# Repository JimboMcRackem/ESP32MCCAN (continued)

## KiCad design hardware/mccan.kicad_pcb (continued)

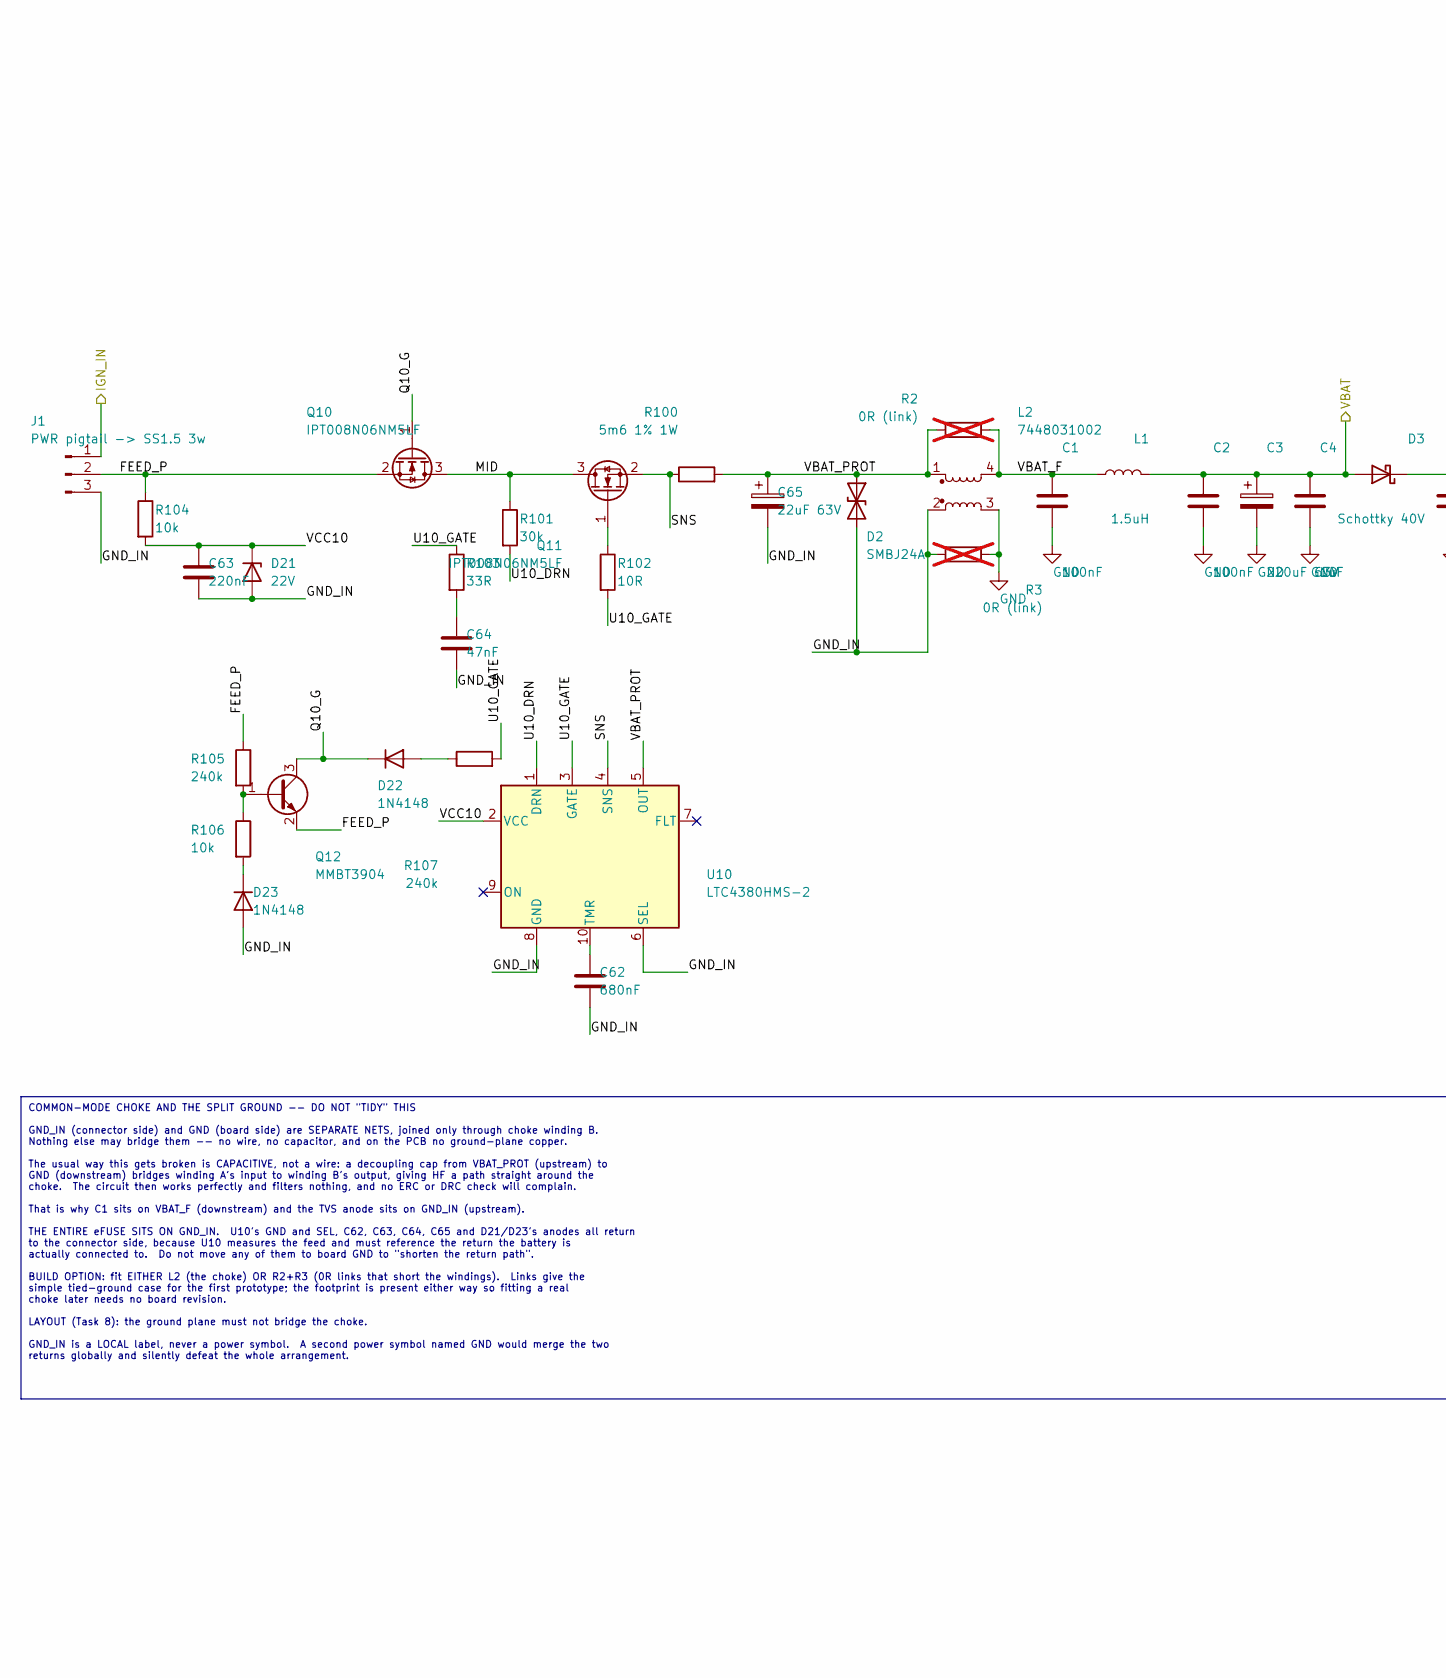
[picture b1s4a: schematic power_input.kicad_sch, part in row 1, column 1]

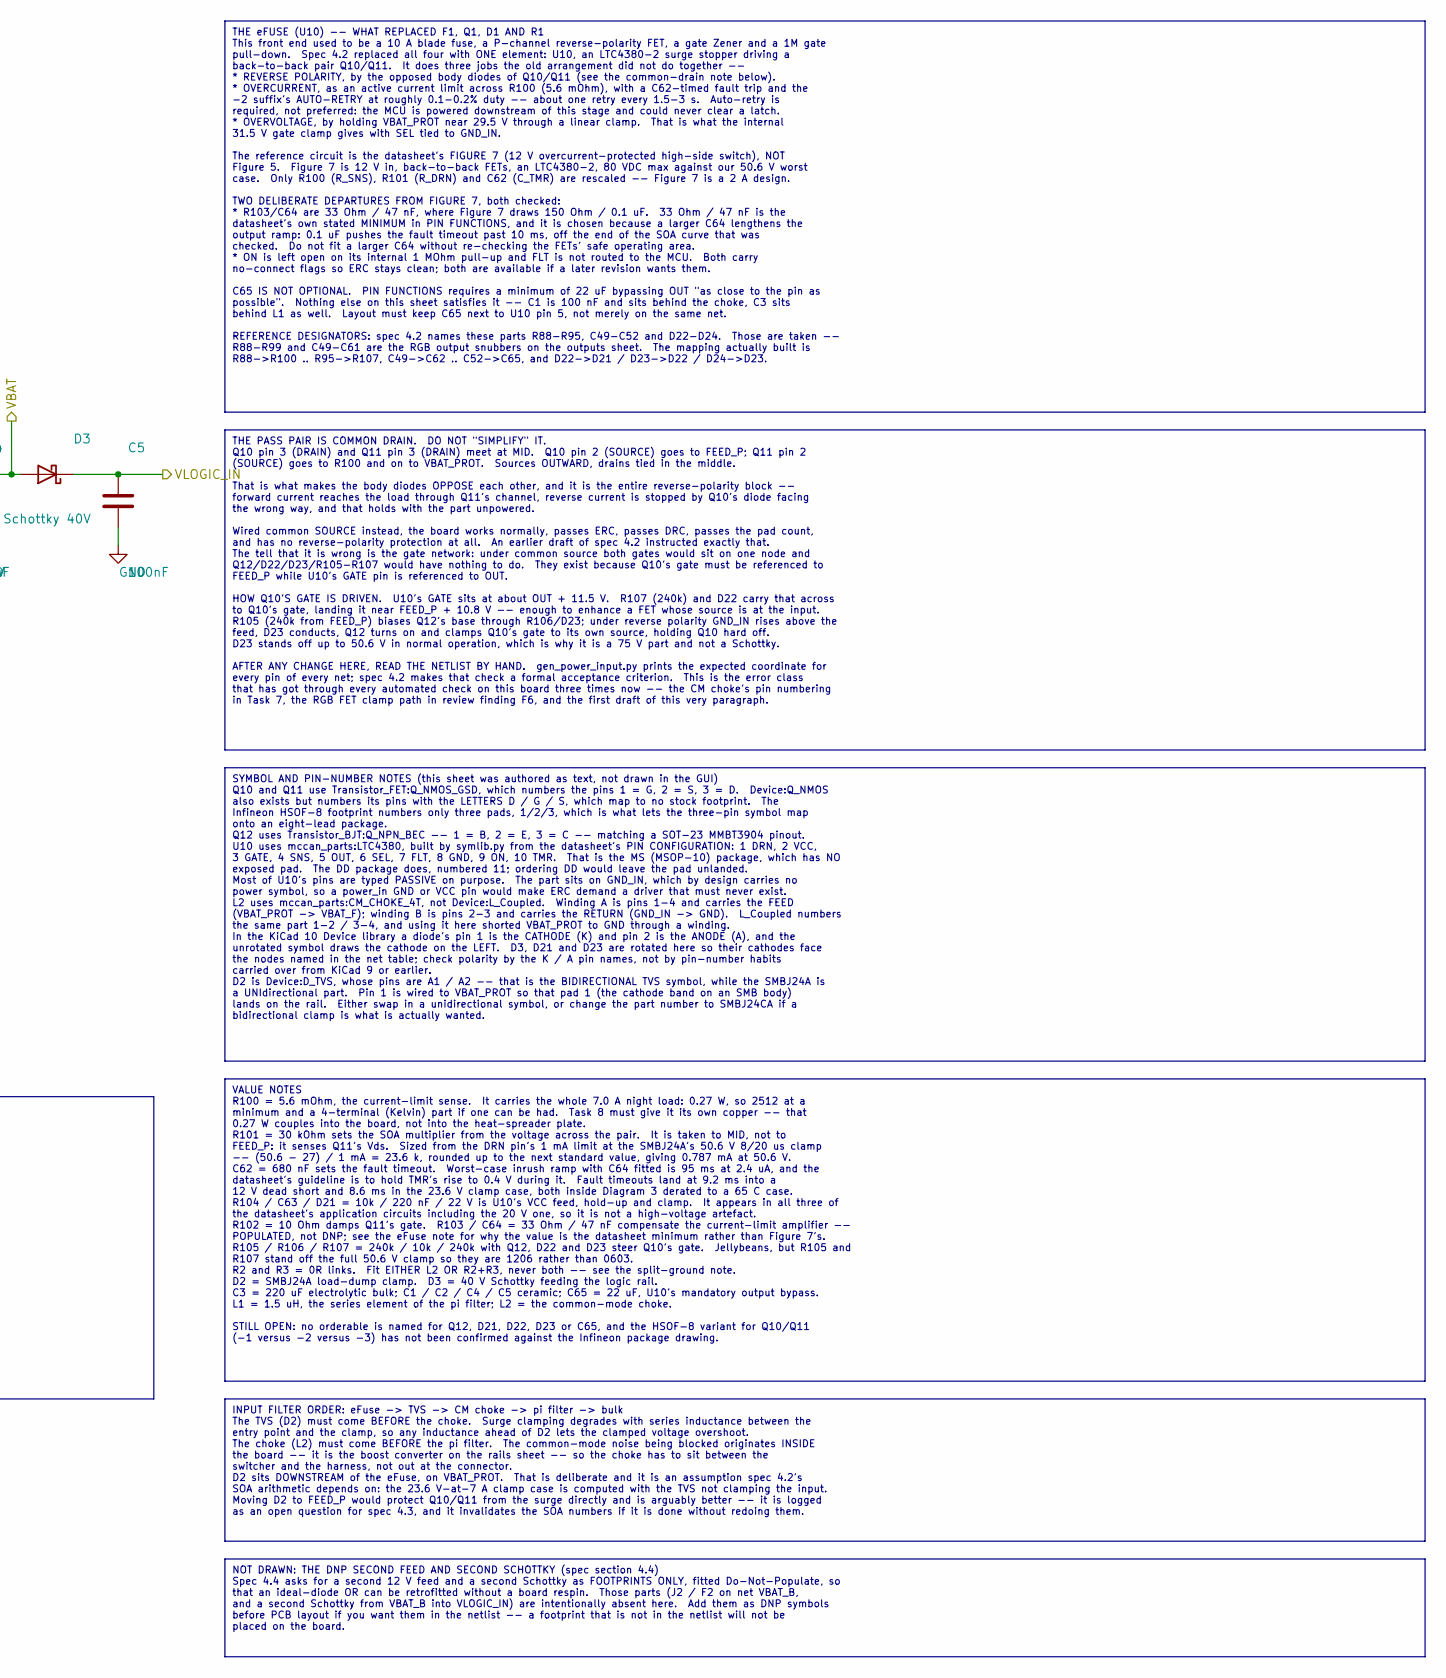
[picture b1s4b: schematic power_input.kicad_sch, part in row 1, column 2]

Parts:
C1: 100nF; C_0603_1608Metric
C2, C5: 100nF; C_0805_2012Metric
C3: 220uF 63V; CP_Elec_10x10.5
C4: 1uF; C_1206_3216Metric
C62: 680nF; C_0603_1608Metric
C63: 220nF; C_0603_1608Metric
C64: 47nF; C_0805_2012Metric
C65: 22uF 63V; CP_Elec_6.3x7.7
D2: SMBJ24A; D_SMB
D3: Schottky 40V; D_SMA
D21: 22V; D_SOD-123
D22, D23: 1N4148; D_SOD-323
J1: PWR pigtail -> SS1.5 3w; SolderWire-1.5sqmm_1x03_P6mm_D1.7mm_OD3mm_Relief
L1: 1.5uH; L_Vishay_IHLP-4040
L2: 7448031002; Wurth_WE-CMBNC_7448031002
Q10, Q11: IPT008N06NM5LF; Infineon_PG-HSOF-8-1
Q12: MMBT3904; SOT-23
R2, R3: 0R (link); R_2512_6332Metric; not fitted
R100: 5m6 1% 1W; R_2512_6332Metric
R101: 30k; R_1206_3216Metric
R102: 10R; R_0603_1608Metric
R103: 33R; R_0603_1608Metric
R104, R106: 10k; R_0603_1608Metric
R105, R107: 240k; R_1206_3216Metric
U10: LTC4380HMS-2; MSOP-10_3x3mm_P0.5mm

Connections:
/IGN_IN: J1.1; also elsewhere on the board
/VBAT: C2.1, C3.1, C4.1, D3.2 (A), L1.2; also elsewhere on the board
/VLOGIC_IN: C5.1, D3.1 (K); also elsewhere on the board
/power_input/FEED_P: J1.2, Q10.2 (S), Q12.2 (E), R104.1, R105.1
/power_input/GND_IN: C62.2, C63.2, C64.2, C65.2, D2.2 (A2), D21.2 (A), D23.2 (A), J1.3, L2.2, R3.1, U10.6 (SEL), U10.8 (GND)
/power_input/MID: Q10.3 (D), Q11.3 (D), R101.1
/power_input/Q10_G: D22.1 (K), Q10.1 (G), Q12.3 (C)
/power_input/SNS: Q11.2 (S), R100.1, U10.4 (SNS)
/power_input/U10_DRN: R101.2, U10.1 (DRN)
/power_input/U10_GATE: R102.2, R103.1, R107.2, U10.3 (GATE)
/power_input/VBAT_F: C1.1, L1.1, L2.4, R2.2
/power_input/VBAT_PROT: C65.1, D2.1 (A1), L2.1, R2.1, R100.2, U10.5 (OUT)
/power_input/VCC10: C63.1, D21.1 (K), R104.2, U10.2 (VCC)
unnamed: C64.1, R103.2
unnamed: D22.2 (A), R107.1
unnamed: D23.1 (K), R106.2
unnamed: Q11.1 (G), R102.1
unnamed: Q12.1 (B), R105.2, R106.1
unnamed: C62.1, U10.10 (TMR)

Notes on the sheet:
VALUE NOTES R100 = 5.6 mOhm, the current-limit sense. It carries the whole 7.0 A night load: 0.27 W, so 2512 at a minimum and a 4-terminal (Kelvin) part if one can be had. Task 8 must give it its own copper -- that 0.27 W couples into the board, not into the heat-spreader plate. R101 = 30 kOhm sets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
INPUT FILTER ORDER: eFuse -> TVS -> CM choke -> pi filter -> bulk The TVS (D2) must come BEFORE the choke. Surge clamping degrades with series inductance between the entry point and the clamp, so any inductance ahead of D2 lets the clamped voltage overshoot. The choke (L2) must come BEFORE the pi f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
THE PASS PAIR IS COMMON DRAIN. DO NOT "SIMPLIFY" IT. Q10 pin 3 (DRAIN) and Q11 pin 3 (DRAIN) meet at MID. Q10 pin 2 (SOURCE) goes to FEED_P; Q11 pin 2 (SOURCE) goes to R100 and on to VBAT_PROT. Sources OUTWARD, drains tied in the middle. That is what makes the body diodes OPPOSE each other, and it 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
THE eFUSE (U10) -- WHAT REPLACED F1, Q1, D1 AND R1 This front end used to be a 10 A blade fuse, a P-channel reverse-polarity FET, a gate Zener and a 1M gate pull-down. Spec 4.2 replaced all four with ONE element: U10, an LTC4380-2 surge stopper driving a back-to-back pair Q10/Q11. It does three job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
SYMBOL AND PIN-NUMBER NOTES (this sheet was authored as text, not drawn in the GUI) Q10 and Q11 use Transistor_FET:Q_NMOS_GSD, which numbers the pins 1 = G, 2 = S, 3 = D. Device:Q_NMOS also exists but numbers its pins with the LETTERS D / G / S, which map to no stock footprint. The Infineon HSOF-8 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
COMMON-MODE CHOKE AND THE SPLIT GROUND -- DO NOT "TIDY" THIS GND_IN (connector side) and GND (board side) are SEPARATE NETS, joined only through choke winding B. Nothing else may bridge them -- no wire, no capacitor, and on the PCB no ground-plane copper. The usual way this gets broken is CAPACITIV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
NOT DRAWN: THE DNP SECOND FEED AND SECOND SCHOTTKY (spec section 4.4) Spec 4.4 asks for a second 12 V feed and a second Schottky as FOOTPRINTS ONLY, fitted Do-Not-Populate, so that an ideal-diode OR can be retrofitted without a board respin. Those parts (J2 / F2 on net VBAT_B, and a second Schottky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

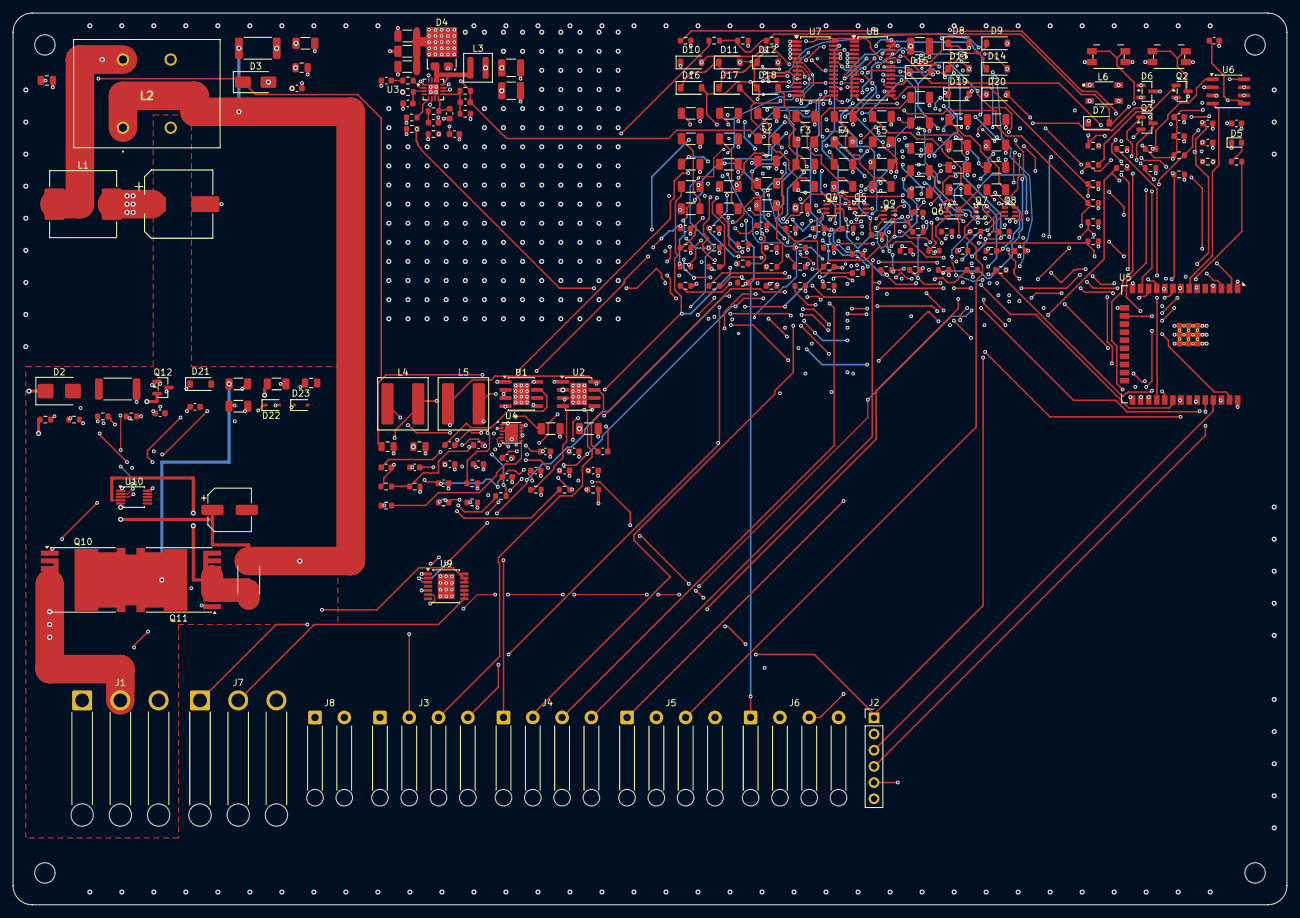
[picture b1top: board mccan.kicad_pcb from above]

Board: 8 copper layers, 200.0 x 140.0 mm, 238 parts (0 on the bottom side), 153 nets.

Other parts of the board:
H1, H2, H3, H4: MountingHole; MountingHole_3.2mm_M3
Q4, Q5, Q6, Q7, Q8, Q9: NX5020UNBKS; SOT-363_SC-70-6

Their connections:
/outputs/PWM_FL_B: Q5.2; also elsewhere on the board
/outputs/PWM_FL_G: Q4.5; also elsewhere on the board
/outputs/PWM_FL_R: Q4.2; also elsewhere on the board
/outputs/PWM_FR_B: Q6.5; also elsewhere on the board
/outputs/PWM_FR_G: Q6.2; also elsewhere on the board
/outputs/PWM_FR_R: Q5.5; also elsewhere on the board
/outputs/PWM_RL_B: Q8.2; also elsewhere on the board
/outputs/PWM_RL_G: Q7.5; also elsewhere on the board
/outputs/PWM_RL_R: Q7.2; also elsewhere on the board
/outputs/PWM_RR_B: Q9.5; also elsewhere on the board
/outputs/PWM_RR_G: Q9.2; also elsewhere on the board
/outputs/PWM_RR_R: Q8.5; also elsewhere on the board
/outputs/RET_FL_R: Q4.6; also elsewhere on the board
/outputs/SENSE_FL_B: Q5.1; also elsewhere on the board
/outputs/SENSE_FL_G: Q4.4; also elsewhere on the board
/outputs/SENSE_FL_R: Q4.1; also elsewhere on the board
/outputs/SENSE_FR_B: Q6.4; also elsewhere on the board
/outputs/SENSE_FR_G: Q6.1; also elsewhere on the board
/outputs/SENSE_FR_R: Q5.4; also elsewhere on the board
/outputs/SENSE_RL_B: Q8.1; also elsewhere on the board
/outputs/SENSE_RL_G: Q7.4; also elsewhere on the board
/outputs/SENSE_RL_R: Q7.1; also elsewhere on the board
/outputs/SENSE_RR_B: Q9.4; also elsewhere on the board
/outputs/SENSE_RR_G: Q9.1; also elsewhere on the board
/outputs/SENSE_RR_R: Q8.4; also elsewhere on the board

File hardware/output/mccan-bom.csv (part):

"Refs","Value","Footprint","Qty","DNP"
"C1","100nF","Capacitor_SMD:C_0603_1608Metric","1",""
"C2","100nF","Capacitor_SMD:C_0805_2012Metric","1",""
"C3","220uF 63V","Capacitor_SMD:CP_Elec_10x10.5","1",""
"C4","1uF","Capacitor_SMD:C_1206_3216Metric","1",""
"C5","100nF","Capacitor_SMD:C_0805_2012Metric","1",""
"C6","2.2uF","Capacitor_SMD:C_1206_3216Metric","1",""
"C7","100nF","Capacitor_SMD:C_0805_2012Metric","1",""
"C8","2.2nF","Capacitor_SMD:C_0603_1608Metric","1",""
"C9","68pF","Capacitor_SMD:C_0603_1608Metric","1",""
"C10","22uF","Capacitor_SMD:C_0603_1608Metric","1",""
"C11","22uF","Capacitor_SMD:C_0603_1608Metric","1",""
"C12","2.2uF","Capacitor_SMD:C_1206_3216Metric","1",""
"C13","100nF","Capacitor_SMD:C_0805_2012Metric","1",""
"C14","2.2nF","Capacitor_SMD:C_0603_1608Metric","1",""
"C15","39pF","Capacitor_SMD:C_0603_1608Metric","1",""
"C16","22uF","Capacitor_SMD:C_0603_1608Metric","1",""
"C17","100nF","Capacitor_SMD:C_0603_1608Metric","1",""
"C18","10uF","Capacitor_SMD:C_1210_3225Metric","1",""
"C19","10uF","Capacitor_SMD:C_1210_3225Metric","1",""
"C20","4.7uF","Capacitor_SMD:C_1206_3216Metric","1",""
"C21","4.7uF","Capacitor_SMD:C_1206_3216Metric","1",""
"C22","4.7uF","Capacitor_SMD:C_1206_3216Metric","1",""
"C23","10nF","Capacitor_SMD:C_0603_1608Metric","1",""
"C24","100pF","Capacitor_SMD:C_0603_1608Metric","1",""
"C25","22nF","Capacitor_SMD:C_0603_1608Metric","1",""
"C26","1uF","Capacitor_SMD:C_0603_1608Metric","1",""
"C27","100nF","Capacitor_SMD:C_0603_1608Metric","1",""
"C28","2.2nF","Capacitor_SMD:C_0603_1608Metric","1",""
"C29","2.2nF","Capacitor_SMD:C_0603_1608Metric","1",""
"C30","1uF","Capacitor_SMD:C_0603_1608Metric","1",""
"C31","1uF","Capacitor_SMD:C_0603_1608Metric","1",""
"C32","1nF","Capacitor_SMD:C_0603_1608Metric","1",""
"C33","100nF","Capacitor_SMD:C_0603_1608Metric","1",""
"C34","10uF","Capacitor_SMD:C_0603_1608Metric","1",""
"C35","10uF","Capacitor_SMD:C_0603_1608Metric","1",""
"C36","100nF","Capacitor_SMD:C_0603_1608Metric","1",""
"C37","1uF","Capacitor_SMD:C_0603_1608Metric","1",""
"C38","100nF","Capacitor_SMD:C_0603_1608Metric","1",""
"C39","100nF","Capacitor_SMD:C_0603_1608Metric","1",""
"C40","100nF","Capacitor_SMD:C_0603_1608Metric","1",""
"C41","10uF","Capacitor_SMD:C_0603_1608Metric","1",""
"C42","100nF","Capacitor_SMD:C_0603_1608Metric","1",""
"C43","100nF","Capacitor_SMD:C_0603_1608Metric","1",""
"C44","10nF","Capacitor_SMD:C_0603_1608Metric","1",""
"C45","10uF","Capacitor_SMD:C_1210_3225Metric","1",""
"C46","100nF","Capacitor_SMD:C_0805_2012Metric","1",""
"C47","220pF","Capacitor_SMD:C_0603_1608Metric","1",""
"C48","10nF","Capacitor_SMD:C_0603_1608Metric","1",""
"C49","10nF","Capacitor_SMD:C_1206_3216Metric","1","DNP"
"C50","10nF","Capacitor_SMD:C_1206_3216Metric","1","DNP"
"C51","10nF","Capacitor_SMD:C_1206_3216Metric","1","DNP"
"C52","10nF","Capacitor_SMD:C_1206_3216Metric","1","DNP"
"C53","10nF","Capacitor_SMD:C_1206_3216Metric","1","DNP"
"C54","10nF","Capacitor_SMD:C_1206_3216Metric","1","DNP"
"C55","10nF","Capacitor_SMD:C_1206_3216Metric","1","DNP"
"C56","10nF","Capacitor_SMD:C_1206_3216Metric","1","DNP"
"C57","10nF","Capacitor_SMD:C_1206_3216Metric","1","DNP"
"C58","10nF","Capacitor_SMD:C_1206_3216Metric","1","DNP"
"C59","10nF","Capacitor_SMD:C_1206_3216Metric","1","DNP"
"C60","10nF","Capacitor_SMD:C_1206_3216Metric","1","DNP"
"C61","10pF","Capacitor_SMD:C_0603_1608Metric","1","DNP"
"C62","680nF","Capacitor_SMD:C_0603_1608Metric","1",""
"C63","220nF","Capacitor_SMD:C_0603_1608Metric","1",""
"C64","47nF","Capacitor_SMD:C_0805_2012Metric","1",""
"C65","22uF 63V","Capacitor_SMD:CP_Elec_6.3x7.7","1",""
"D2","SMBJ24A","Diode_SMD:D_SMB","1",""
"D3","Schottky 40V","Diode_SMD:D_SMA","1",""
"D4","SS5PH102","Package_TO_SOT_SMD:TO-277A","1",""
"D5","green","LED_SMD:LED_0603_1608Metric","1",""
"D6","PESD2CANFD24U-T","Package_TO_SOT_SMD:SOT-23","1",""
"D7","BAT54","Diode_SMD:D_SOD-123","1",""
"D8","BAT54","Diode_SMD:D_SOD-123","1",""
"D9","BAT54","Diode_SMD:D_SOD-123","1",""
"D10","BAT54","Diode_SMD:D_SOD-123","1",""
"D11","BAT54","Diode_SMD:D_SOD-123","1",""
"D12","BAT54","Diode_SMD:D_SOD-123","1",""
"D13","BAT54","Diode_SMD:D_SOD-123","1",""
"D14","BAT54","Diode_SMD:D_SOD-123","1",""
"D15","BAT54","Diode_SMD:D_SOD-123","1",""
"D16","BAT54","Diode_SMD:D_SOD-123","1",""
"D17","BAT54","Diode_SMD:D_SOD-123","1",""
"D18","BAT54","Diode_SMD:D_SOD-123","1",""
"D19","BAT54","Diode_SMD:D_SOD-123","1",""
"D20","BAT54","Diode_SMD:D_SOD-123","1",""
"D21","22V","Diode_SMD:D_SOD-123","1",""
"D22","1N4148","Diode_SMD:D_SOD-323","1",""
"D23","1N4148","Diode_SMD:D_SOD-323","1",""
"F2","1206L050/24","Fuse:Fuse_1206_3216Metric","1",""
"F3","1206L050/24","Fuse:Fuse_1206_3216Metric","1",""
"F4","1206L050/24","Fuse:Fuse_1206_3216Metric","1",""
"F5","1206L050/24","Fuse:Fuse_1206_3216Metric","1",""
"J2","Prog/UART","Connector_PinHeader_2.54mm:PinHeader_1x06_P2.54mm_Vertical","1",""
"L1","1.5uH","Inductor_SMD:L_Vishay_IHLP-4040","1",""
"L2","7448031002","mccan:Wurth_WE-CMBNC_7448031002","1",""
"L3","6.8uH XAL4030-682ME","Inductor_SMD:L_Coilcraft_XAL4030-XXX","1",""
"L4","XAL7070-223ME","Inductor_SMD:L_Coilcraft_XAL7070-XXX","1",""
"L5","XAL7070-223ME","Inductor_SMD:L_Coilcraft_XAL7070-XXX","1",""
"L6","ACT45B-510-2P-TL003","mccan:TDK_ACT45B","1",""
"Q2","MMBT3904","Package_TO_SOT_SMD:SOT-23","1",""
"Q3","MMBT3904","Package_TO_SOT_SMD:SOT-23","1",""
"Q4","NX5020UNBKS","Package_TO_SOT_SMD:SOT-363_SC-70-6","1",""
"Q5","NX5020UNBKS","Package_TO_SOT_SMD:SOT-363_SC-70-6","1",""
"Q6","NX5020UNBKS","Package_TO_SOT_SMD:SOT-363_SC-70-6","1",""
"Q7","NX5020UNBKS","Package_TO_SOT_SMD:SOT-363_SC-70-6","1",""
"Q8","NX5020UNBKS","Package_TO_SOT_SMD:SOT-363_SC-70-6","1",""
"Q9","NX5020UNBKS","Package_TO_SOT_SMD:SOT-363_SC-70-6","1",""
"Q10","IPT008N06NM5LF","Package_TO_SOT_SMD:Infineon_PG-HSOF-8-1","1",""
"Q11","IPT008N06NM5LF","Package_TO_SOT_SMD:Infineon_PG-HSOF-8-1","1",""
"Q12","MMBT3904","Package_TO_SOT_SMD:SOT-23","1",""
"R2","0R (link)","Resistor_SMD:R_2512_6332Metric","1","DNP"
"R3","0R (link)","Resistor_SMD:R_2512_6332Metric","1","DNP"
"R4","20.5k","Resistor_SMD:R_0603_1608Metric","1",""
"R5","348k","Resistor_SMD:R_0603_1608Metric","1",""
"R6","200k","Resistor_SMD:R_0603_1608Metric","1",""
"R7","31.6k","Resistor_SMD:R_0603_1608Metric","1",""
"R8","634k","Resistor_SMD:R_0603_1608Metric","1",""
"R9","200k","Resistor_SMD:R_0603_1608Metric","1",""
"R10","9.09k","Resistor_SMD:R_0603_1608Metric","1",""
"R11","37.4k","Resistor_SMD:R_0603_1608Metric","1",""
"R12","576k","Resistor_SMD:R_0603_1608Metric","1",""
"R13","24.9k","Resistor_SMD:R_0603_1608Metric","1",""
"R14","2.61k","Resistor_SMD:R_0603_1608Metric","1",""
"R15","5.1R","Resistor_SMD:R_0603_1608Metric","1",""
"R16","0R","Resistor_SMD:R_0603_1608Metric","1",""
"R17","133k","Resistor_SMD:R_0603_1608Metric","1",""
"R18","174k","Resistor_SMD:R_0603_1608Metric","1",""
"R19","100k","Resistor_SMD:R_0603_1608Metric","1",""
"R20","100k","Resistor_SMD:R_0603_1608Metric","1",""
"R21","100R","Resistor_SMD:R_0603_1608Metric","1",""
"R22","10k","Resistor_SMD:R_0603_1608Metric","1",""
"R23","0R","Resistor_SMD:R_0603_1608Metric","1","DNP"
"R24","10k","Resistor_SMD:R_0603_1608Metric","1",""
"R25","10k","Resistor_SMD:R_0603_1608Metric","1",""
"R26","120R","Resistor_SMD:R_0603_1608Metric","1","DNP"
"R27","1k","Resistor_SMD:R_0603_1608Metric","1",""
"R28","10k","Resistor_SMD:R_0603_1608Metric","1",""
"R29","10k","Resistor_SMD:R_0603_1608Metric","1",""
"R30","10k","Resistor_SMD:R_0603_1608Metric","1",""
"R31","10k","Resistor_SMD:R_0603_1608Metric","1",""
"R32","10k","Resistor_SMD:R_0603_1608Metric","1",""
"R33","10k","Resistor_SMD:R_0603_1608Metric","1",""
"R34","10k","Resistor_SMD:R_0603_1608Metric","1",""
"R35","10k","Resistor_SMD:R_0603_1608Metric","1",""
"R36","10k","Resistor_SMD:R_0603_1608Metric","1",""
"R37","90.9k","Resistor_SMD:R_0603_1608Metric","1","DNP"
"R38","33k","Resistor_SMD:R_0603_1608Metric","1","DNP"
"R39","100k","Resistor_SMD:R_0603_1608Metric","1",""
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
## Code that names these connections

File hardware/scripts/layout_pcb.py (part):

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     "eFuse island near J1, and NOT via-coupled to the plate: U10, Q10, Q11, R100, C65.\n"
     "R100 needs its own copper and a Kelvin tap. C65 must sit AT U10 pin 5.\n"
     "Antenna edge is RIGHT: no copper, plating or parts on ANY layer in the U5 keep-out.\n"
     # J8 carries /CANH and /CANL (x 67.4); J2 is the 6-pin PROGRAMMING header (x 155.17,
     # /+3V3_ALW, DTR, RTS, UART_RX, UART_TX, GND).  Read off the board's own footprint nets.
     # The note used to say "J2 CAN at the far right", which named the wrong connector as the
     # one needing the CAN gland and the separation from the power connector.
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    # The chain -- J1 -> Q10 -> Q11 -> R100 -> L2 -> L1 -> the In3.Cu plane -- is hand-laid
    # in ROUTES at an explicit 3.5 mm, segment by segment, because it is the only part of
    # these nets that ever sees 7 A.  Everything else on them is a tap: gate-drive bias to
    # R104/R105/Q12, the MID sense divider, the Kelvin pair to U10 pins 4 and 5, D2's clamp,
    # decoupling.  Those land on 0603 pads inside the eFuse control band, and the widest
    # slot in that band is 0.95 mm.  A 3.5 mm class width does not make a tap wide -- it
    # makes it unroutable, and that is what 51 of the 72 unconnected items were.
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    # obstacles between the two pads at y=50.
    ("VBAT", "F.Cu", 4.5, [(35.5085, 50.0), (41.8, 50.0)]),

    # ===================== U10 Kelvin pair (SNS pin 4, VBAT_PROT pin 5) =====================
    # U10 is a 10-pad, 0.5 mm pitch part -- gen_pcb's dru_floor() relaxes clearance
    # between a hand track and a U10 *pad* to 0.18-0.2 mm for exactly this reason, but it
    # does NOT relax clearance between two hand tracks that both happen to be near U10.
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    # output-bypass cap) before continuing on to the trunk -- notes_power_input.py is
    # explicit that neither line may hang a spur off the sense run instead.

    # SNS / pin 4: 0.3 mm reached only 0.075 mm clear of U10.1-3's pads once the
    # exemption's own floor (0.12 mm) is applied, and even inside the exemption the
    # round end-cap of pin 5's escape (0.5 mm pitch away) came out only 0.1 mm clear
    # of THIS track -- track-vs-track is never exempted.  The board's own track-width
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    # VBAT_PROT trunk's own 4.5 mm copper (x=57-73), and x=54 sits inside VBAT_PROT's
    # C65-to-trunk jog (x=51.3-57 at y=103.5).
    ("SNS", "F.Cu", 0.5, [(35.5, 96.5), (35.5, 93.0), (48.3, 93.0), (48.3, 98.5)]),
    # x=48.3 also crosses VBAT_PROT's OTHER jog -- pin 5's run from its own escape to
    # C65 sits at y=99.5, spanning x=36.9-51.3, which x=48.3 is inside.  SNS carries no
    # real current, so a two-via hop to duck under it on In5.Cu (clear here -- the
    # FEED_P taps' In5.Cu columns are at x=24/41/59.5, none of them 48.3) is cheaper
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    ("SNS", "In5.Cu", 0.5, [(48.3, 98.5), (48.3, 100.5)]),
    ("SNS", "F.Cu", 0.5, [(48.3, 100.5), (48.3, 109.0), (57.0, 109.0), (57.0, 111.9625)]),

    # VBAT_PROT / pin 5: straight south into open space below the part.  The corner
    # pin has no U10 neighbour on that side, but pin 4's escape (above) starts only
    # 0.5 mm away at the shared column x=36.9 -- same fix, 0.2 mm (the board's track-
    # width floor) for the first hop so the two tracks' end-caps clear each other by
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    # x=48.3, none of them x=36.9.  Re-verified with the same pcbnew filler: 1 island,
    # bbox x=[22,71] y=[36,149.5] -- the whole zone, GNDIN_F whole again.
    #
    # This also answers the review's Important-3 concern (SNS pin 4's 0.2 mm escape vs
    # this pin's own 0.2 mm hop above, stacking both the width and clearance floors at
    # once): moving pin 5 to an inner-layer via sooner, as the review suggested, was
    # tried and measured worse, not better.  The two 0.2 mm hops' own end-caps (fixed by
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    # protection) and R26 are reached by short hops and a stub off that same copper, not by
    # passing through them in series -- see the "D6 -> R26 -> L6 cluster" comment further down
    # for why, and gen_mcu_can.py around lines 341-351 for why: R26 is a DNP 120-ohm shunt
    # straight across the CANH/CANL labels, not a series split termination.  All twelve pad
    # coordinates are the brief's measured figures, used verbatim.
    #
    # In2.Cu is empty apart from via barrels, so there is no F.Cu-style footprint/silk field to
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    # unchanged to the digit; they are simply no longer the tightest thing on the run.
    #
    # Each track is offset +-0.325 mm from that centreline (perpendicular to its 38.2 deg
    # bearing), so CANH and CANL hold an exact constant 0.650 mm centre-to-centre and never
    # move independently -- there is nothing to "turn together" because there is nothing to
    # turn, for as much of the run as the centreline model holds. At the J8 end it holds all
    # the way in: the fan-in bend sits 2 mm off the pads (J8.2's keepout constrains CANH's fan
    # to x <= 70.50 while y is in its 129.5-132.0 band -- this fan point lands at x = 68.77,
    # comfortably inside it -- CANL leaves from J8.2 itself so its own pad constrains it not at
    # all).
    #
    # At the L6 end the centreline model runs into a real fixed obstacle the brief's corridor
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    # is geometrically unroutable on one layer as a plain 3-node chain.
    #
    # gen_mcu_can.py resolves this: R26 is a DNP 120-ohm bus terminator wired as a shunt
    # directly across the CANH and CANL labels (`w((284.48,109.22),(284.48,114.3)); lab("CANH",..)`
    # ... `vpart("R26",...,dnp=True)` ... `w(b,(284.48,127.0)); lab("CANL",..)`), not an inline
    # series element in either leg. Electrically the only copper that has to be continuous is
    # D6.1-L6.4 (CANH) and D6.2-L6.3 (CANL); R26's pads are branch stubs off that copper, not
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                              (205.0183, 40.3122), (206.6046, 41.7257)]),
    ("CANL", "In2.Cu", 0.3, [(206.6046, 41.7257), (208.405, 43.330)]),

    # L6 -> U6 ("Net-(U6-CANH)", "Net-(U6-CANL)"): the transceiver side, L6 pins 1/2 to U6's
    # CANH/CANL pins. L6.1/L6.2 sit at very nearly the same y as D6.1/D6.2 (the CANH_main/
    # CANL_main hop above), so a path that runs alongside that hop east would thread directly
    # through D6's own pads (including D6.3) and Q2 -- the same cluster the D6/R26/L6 stubs
    # above already have to route around. Instead this hop goes north of the whole D6/Q2/R26
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    ("Net-(U3-COMP)", "F.Cu", 0.25, [(86.750, 33.4562), (87.0, 33.7), (87.0, 34.6),
                                       (86.825, 35.400), (88.550, 35.025)]),

    # FB_24V: the only F.Cu run this net needs is pin 9 out to a trunk that ties
    # R12.2/C61.2/R13.1 together, which is the far end of the output-cap divider,
    # satisfying the controller's "tap the far end".
    #
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    # is what moved these numbers: the figures here were first written before MODE existed,
    # and MODE now runs alongside SS for its whole length, so MODE is the tightest neighbour
    # of three of SS's five features. Tightest neighbour per leg, all on a 0.200 mm limit:
    #   pin-10 row       0.250 mm to pin 11, to pin 9 and to the FB_24V hop
    #   jog south        0.250 mm to the FB_24V hop
    #   In5.Cu run       0.400 mm to MODE's via at (88.400, 31.200), then 0.491 mm to the
    #                    GND drop via at (87.625, 36.575)
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    # mccan.kicad_pro and the gate ran --severity-error, which discards warnings.
    #
    # Tightest neighbour per leg, measured against the generated board:
    #   east out of pad  0.250 mm to the SW_BOOST hop, 0.275 mm to pin 10's and pin 12's pads
    #   diagonal         0.218 mm to pin 12's pad (the binding measurement on this net)
    #   jog to the via   0.252 mm to the SS duck-under via at (88.600, 32.000)
    #   In2.Cu south     0.253 mm to that same SS via on the long leg -- the tightest of the
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                                     (108.450, 93.700), (108.750, 93.400)]),
    ("Net-(U4-SR)", "In5.Cu", 0.20, [(108.750, 93.400), (110.305, 91.830)]),

    # /EN_BOOST: U3 pin 6 down to R20.1. This is the tightest net in this batch and the
    # only one planned to the class limit itself rather than with the 0.005 mm planning
    # margin the others carry: pin 6's sole escape is the channel between pin 5's pad
    # corner (85.375, 33.875) and pin 7 on the other side, and that channel leaves
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    # Width is 0.20 mm, the board floor, not the router's 0.25: in this corridor 0.25 loses
    # the lane outright, and a load-switch gate carries no current worth the copper.

    # /power_input/U10_GATE: U10 pin 3 down to the router's own via at (38.300, 83.600),
    # 14.5 mm, F.Cu -> In5.Cu. The easy one in this batch: this is the input-protection
    # cluster, not the output field, and the channel south at x = 39.20..39.45 was still open.
    #
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    # The committed /outputs/PWM_FL_R route that used to sit here has been REMOVED, and this
    # batch re-routes that net from scratch. It was not wrong; it was first. U7 pins 6 and 7
    # are 0.650 mm apart and both escape eastward through the same pocket, and the route that
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
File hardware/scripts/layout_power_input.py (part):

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#   2. THE INPUT FILTER (spec 4.3), unchanged apart from being shifted 73.66 mm right to
#      make room.  D2 TVS -> L2 common-mode choke -> C1 -> L1 -> bulk -> D3 -> VLOGIC_IN.
#
#  y =  64.77 : Q10_G label stub
#  y =  69.85 : R2 (0R link across choke winding A)
#  y =  76.20 : main feed rail  FEED_P .. MID .. SNS .. VBAT_PROT | L2-A | VBAT_F .. VBAT
#  y =  81.28 : L2 winding B    (GND_IN on pin 2, board GND on pin 3)
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#  y = 110-157: the eFuse block -- U10, its gate network and its passives
#
# ---------------------------------------------------------------- THE PASS PAIR
# Q10 and Q11 are COMMON DRAIN: pin 3 (D) of both meets at MID, pin 2 (S) of Q10 goes to
# FEED_P and pin 2 (S) of Q11 goes to R100/SNS.  Their body diodes then oppose each other,
# which is the reverse-polarity block and holds with the part unpowered.
#
# Wiring them common SOURCE instead passes ERC, passes DRC, passes the pad count, and
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    ((31.75, 76.20), (38.10, 76.20)),        # FEED_P : J1.1 -> R104 tap
    ((38.10, 76.20), (38.10, 78.74)),        #          down to R104.1
    ((38.10, 76.20), (71.12, 76.20)),        #          on to Q10 pin 2 (SOURCE)
    ((81.28, 76.20), (90.17, 76.20)),        # MID : Q10 pin 3 (DRAIN) -> R101 tap
    ((90.17, 76.20), (90.17, 80.01)),        #       down to R101.1
    ((90.17, 76.20), (99.06, 76.20)),        #       on to Q11 pin 3 (DRAIN)
    ((109.22, 76.20), (113.03, 76.20)),      # SNS : Q11 pin 2 (SOURCE) -> R100.1
    ((113.03, 76.20), (113.03, 83.82)),      #       stub down to the SNS label
    ((120.65, 76.20), (127.00, 76.20)),      # VBAT_PROT : R100.2 -> C65
    ((127.00, 76.20), (139.70, 76.20)),      #             on to D2 cathode
    ((139.70, 76.20), (149.86, 76.20)),      #             on to L2 winding A in
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    ((31.75, 78.74), (31.75, 88.90)),        # J1.2 down to its GND_IN label

    # ---------------------------------------------------------------- U10 sense taps
    ((90.17, 87.63), (90.17, 91.44)),        # R101.2 down to the U10_DRN label
    ((76.20, 86.36), (82.55, 86.36)),        # R103.1 across to the U10_GATE label
    ((82.55, 93.98), (82.55, 96.52)),        # R103.2 -> C64.1
    ((82.55, 104.14), (82.55, 106.68)),      # C64.2 -> GND_IN
    ((104.14, 83.82), (104.14, 86.36)),      # Q11 pin 1 (GATE) -> R102.1
    ((104.14, 93.98), (104.14, 97.79)),      # R102.2 -> the U10_GATE label

    # ---------------------------------------------------------------- U10 itself
    ((93.98, 118.11), (93.98, 114.30)),      # pin 1  DRN
    ((99.06, 118.11), (99.06, 114.30)),      # pin 3  GATE
    ((104.14, 118.11), (104.14, 114.30)),    # pin 4  SNS
    ((109.22, 118.11), (109.22, 114.30)),    # pin 5  OUT
    ((86.36, 125.73), (80.01, 125.73)),      # pin 2  VCC
    ((93.98, 143.51), (93.98, 147.32)),      # pin 8  GND
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    ((109.22, 147.32), (115.57, 147.32)),

    # ---------------------------------------------------------------- Q10's gate network
    ((59.69, 127.00), (66.04, 127.00)),      # Q12 pin 2 (EMITTER) -> FEED_P
    ((59.69, 116.84), (63.50, 116.84)),      # Q12 pin 3 (COLLECTOR) -> the Q10_G tee
    ((63.50, 116.84), (69.85, 116.84)),      #      -> D22 cathode
    ((63.50, 116.84), (63.50, 113.03)),      #      -> the Q10_G label
    ((77.47, 116.84), (81.28, 116.84)),      # D22 anode -> R107.1
    ((88.90, 116.84), (88.90, 111.76)),      # R107.2 -> the U10_GATE label
    ((52.07, 114.30), (52.07, 110.49)),      # R105.1 -> FEED_P
    ((52.07, 124.46), (52.07, 121.92)),      # R106.1 -> Q12 pin 1 (BASE)
    ((52.07, 132.08), (52.07, 133.35)),      # R106.2 -> D23 cathode
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
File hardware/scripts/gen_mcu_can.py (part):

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L6 = place("L6", "mccan_parts:CM_CHOKE_4T", "ACT45B-510-2P-TL003", 284.48, 95.25, 0, COUPLED,
           [("Reference", "L6", 284.48, 88.9, 0), ("Value", "ACT45B-510-2P-TL003", 284.48, 101.6, 0)],
           desc="Coupled inductor, common-mode choke")
# CANH enters winding A at pin 1 and leaves at pin 4; CANL enters winding B at pin 2 and
# leaves at pin 3.  Geometrically identical to before -- only the pin numbers changed.
w(U6["7"], L6["1"])
w(U6["6"], L6["2"])
# ONE dual-line protector, not two discretes.  The Nexperia PESD2CANFD24U-T is a single
# SOT23 holding both bidirectional elements: pin 1 (K1) on CANH, pin 2 (K2) on CANL,
# pin 3 (CC) the common node to GND.  Replaced the placeholder D6/D7 pair on 2026-09-19;
# `part-selection.md` records why a single dual-line part is preferred over two discretes.
# VRWM 24 V, VCL 33 V typ at 1 A (8/20 us), Cd 3.5 pF, AEC-Q101.
#
# The two protected pins land exactly on the CANH and CANL runs, so each run is drawn as
# TWO segments meeting AT the pin rather than one segment the pin happens to touch.  A
# pin sitting mid-wire does connect, but this sheet has already produced one silent
# connectivity defect of that shape, so the pin is made a wire endpoint and junctioned.
PESD = {"1": (-7.62, 2.54), "2": (-7.62, -2.54), "3": (0.0, -10.16)}
D6 = place("D6", "mccan_parts:PESD2CANFD24U", "PESD2CANFD24U-T", 302.26, 95.25, 0, PESD,
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- Module powered from +3V3_ALW so it stays up in sleep.
- Pin assignment EXACTLY per the plan4 pin map (D2): twelve OUT_* lamp outputs, EN_5V,
  three shared diagnostic lines, SNS_A/B/C on ADC1 (GPIO 34/36/39, input-only).
- CAN_RXD on GPIO 35 (RTC-capable, EXT0 wake).  Ignition sense is gone (spec 6.2).
- CAN_STB on GPIO 14, PULLED UP to VIO (floating = standby).
- TJA1042T/3 TXD has NO connection to any GPIO; it is only pulled up to VIO.
- NO 120 ohm terminator populated; unpopulated footprint present.
- CAN common-mode choke + ESD protection on CANH/CANL.
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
